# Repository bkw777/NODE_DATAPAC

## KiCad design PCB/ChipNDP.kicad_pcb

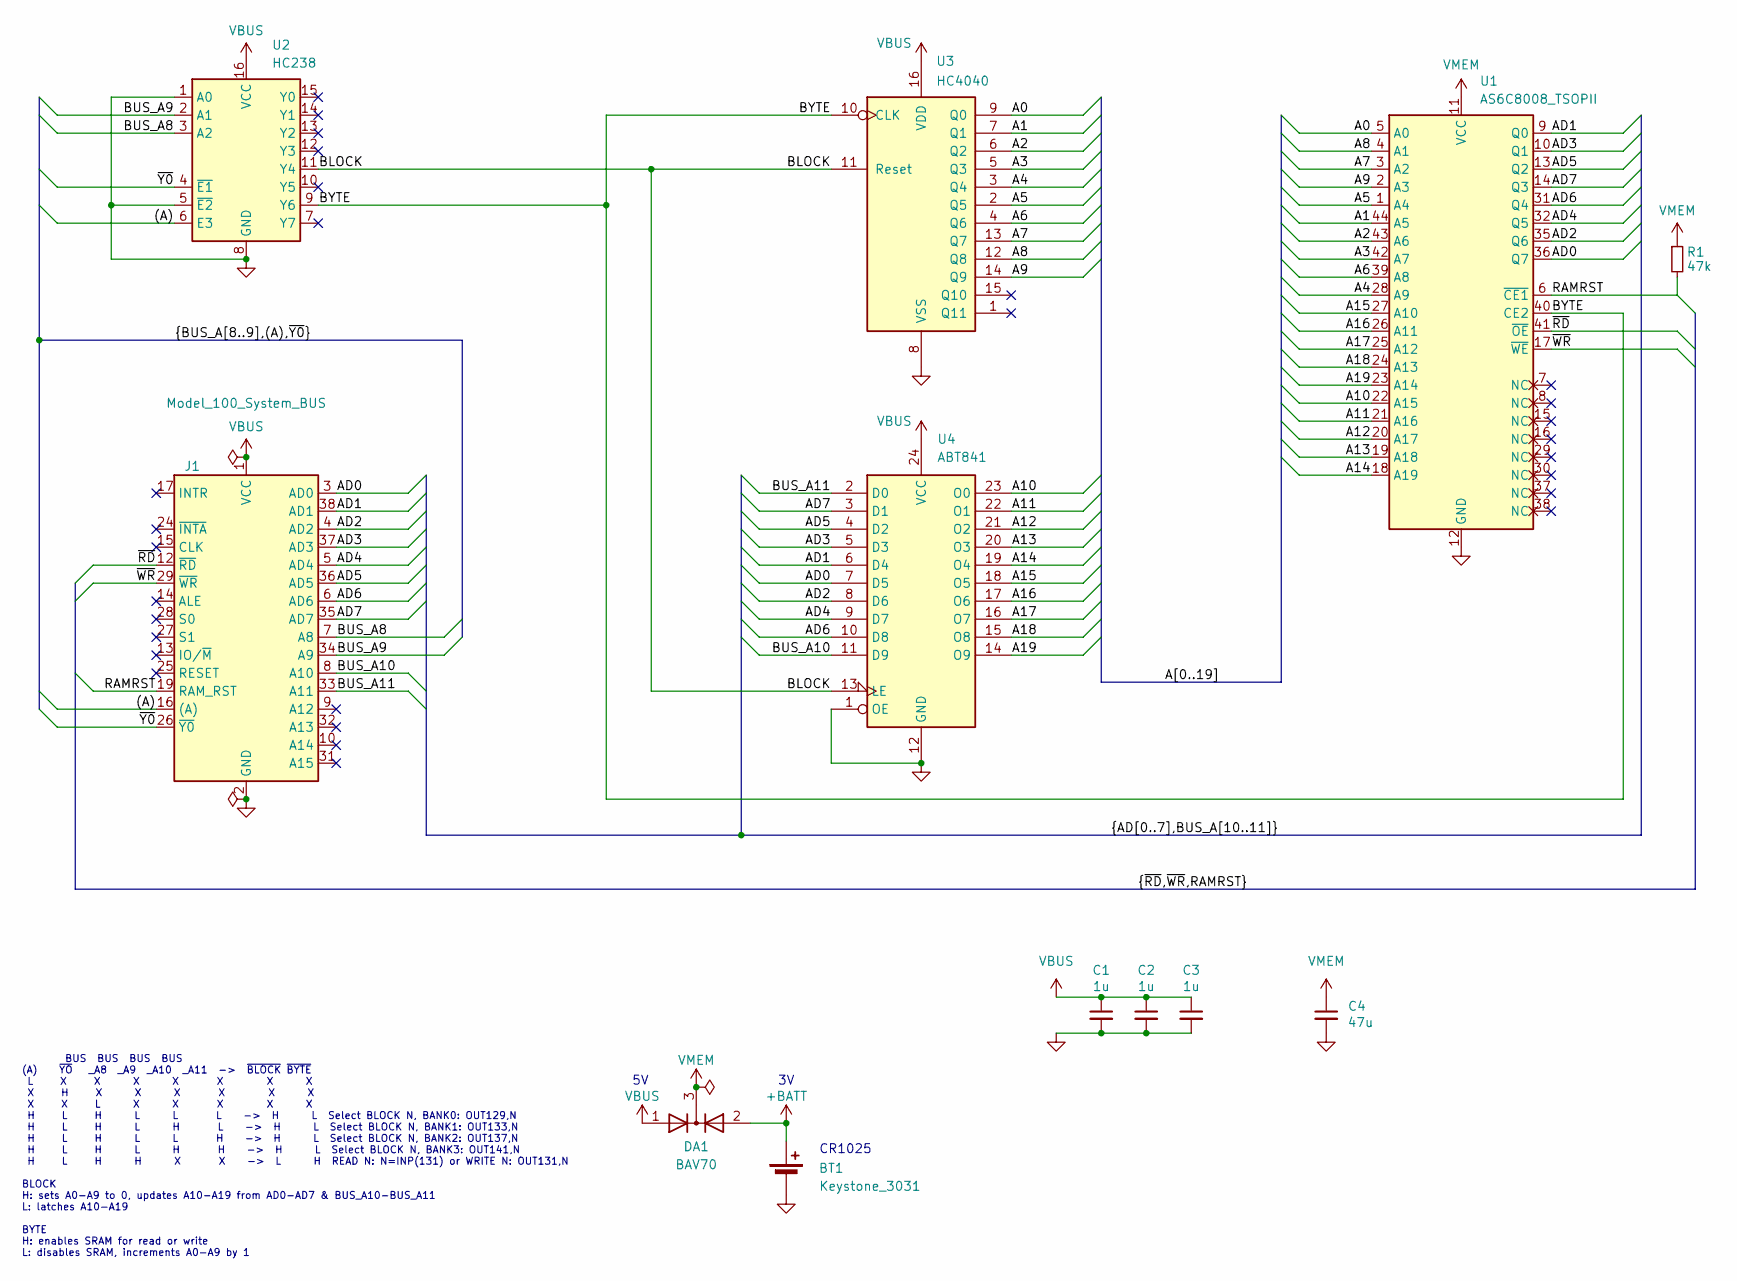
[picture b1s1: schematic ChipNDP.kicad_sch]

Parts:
BT1: Keystone_3031; MPN Keystone 3031
C1, C2, C3: 1u; C_0805; MPN CL21B105KAFNNNE
C4: 47u; C_1206; MPN C3216X5R1E476M160DC
DA1: BAV70; SOT-23; MPN BAV70-7-F
J1: Model_100_System_BUS; DIP-40_PCB; MPN 920-0172-01
R1: 47k; R_0805; MPN RMCF0805FT47K0
U1: AS6C8008_TSOPII; TSOP-II-44; MPN AS6C8008-55ZIN
U2: HC238; TSSOP-16; MPN 74HC238PW,118
U3: HC4040; TSSOP-16; MPN 74HC4040PW,118
U4: ABT841; TSSOP-24_4.4x7.8mm_P0.65mm; MPN SN74ABT841APW

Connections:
+BATT: BT1.1 (+), DA1.2 (A)
/(A): J1.16 ((A)), U2.6 (E3)
/A0: U1.5 (A0), U3.9 (Q0)
/A1: U1.44 (A5), U3.7 (Q1)
/A2: U1.43 (A6), U3.6 (Q2)
/A3: U1.42 (A7), U3.5 (Q3)
/A4: U1.28 (A9), U3.3 (Q4)
/A5: U1.1 (A4), U3.2 (Q5)
/A6: U1.39 (A8), U3.4 (Q6)
/A7: U1.3 (A2), U3.13 (Q7)
/A8: U1.4 (A1), U3.12 (Q8)
/A9: U1.2 (A3), U3.14 (Q9)
/A10: U1.22 (A15), U4.23 (O0)
/A11: U1.21 (A16), U4.22 (O1)
/A12: U1.20 (A17), U4.21 (O2)
/A13: U1.19 (A18), U4.20 (O3)
/A14: U1.18 (A19), U4.19 (O4)
/A15: U1.27 (A10), U4.18 (O5)
/A16: U1.26 (A11), U4.17 (O6)
/A17: U1.25 (A12), U4.16 (O7)
/A18: U1.24 (A13), U4.15 (O8)
/A19: U1.23 (A14), U4.14 (O9)
/AD0: J1.3 (AD0), U1.36 (Q7), U4.7 (D5)
/AD1: J1.38 (AD1), U1.9 (Q0), U4.6 (D4)
/AD2: J1.4 (AD2), U1.35 (Q6), U4.8 (D6)
/AD3: J1.37 (AD3), U1.10 (Q1), U4.5 (D3)
/AD4: J1.5 (AD4), U1.32 (Q5), U4.9 (D7)
/AD5: J1.36 (AD5), U1.13 (Q2), U4.4 (D2)
/AD6: J1.6 (AD6), U1.31 (Q4), U4.10 (D8)
/AD7: J1.35 (AD7), U1.14 (Q3), U4.3 (D1)
/BLOCK: U2.11 (Y4), U3.11 (Reset), U4.13 (LE)
/BUS_A8: J1.7 (A8), U2.3 (A2)
/BUS_A9: J1.34 (A9), U2.2 (A1)
/BUS_A10: J1.8 (A10), U4.11 (D9)
/BUS_A11: J1.33 (A11), U4.2 (D0)
/BYTE: U1.40 (CE2), U2.9 (Y6), U3.10 (CLK)
/RAMRST: J1.19 (RAM_RST), R1.2, U1.6 (~CE1)
/~RD: J1.12 (~RD), U1.41 (~OE)
/~WR: J1.29 (~WR), U1.17 (~WE)
/~Y0: J1.26 (~Y0), U2.4 (~E1)
GND: BT1.2 (-), C1.2, C2.2, C3.2, C4.2, J1.2 (GND), J1.11 (GND), J1.18 (GND), J1.23 (GND), J1.30 (GND), J1.39 (GND), U1.12 (GND), U1.34 (GND), U2.1 (A0), U2.5 (~E2), U2.8 (GND), U3.8 (VSS), U4.1 (OE), U4.12 (GND)
VBUS: C1.1, C2.1, C3.1, DA1.1 (A), J1.1 (VCC), J1.40 (VCC), U2.16 (VCC), U3.16 (VDD), U4.24 (VCC)
VMEM: C4.1, DA1.3 (K), R1.1, U1.11 (VCC), U1.33 (VCC)

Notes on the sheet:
BUS BUS BUS BUS (A) ~{YO} _A8 _A9 _A10 _A11 -> ~{BLOCK} ~{BYTE} L X X X X X X X X H X X X X X X X X L X X X X X H L H L L L -> H L Select BLOCK N, BANK0: OUT129,N H L H L H L -> H L Select BLOCK N, BANK1: OUT133,N H L H L L H -> H L Select BLOCK N, BANK2: OUT137,N H L H L H H -> H L Select BLOCK N,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
CR1025

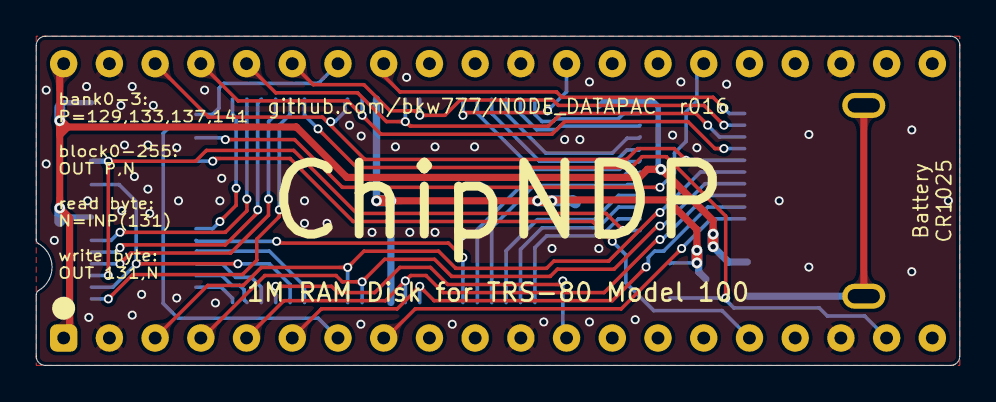
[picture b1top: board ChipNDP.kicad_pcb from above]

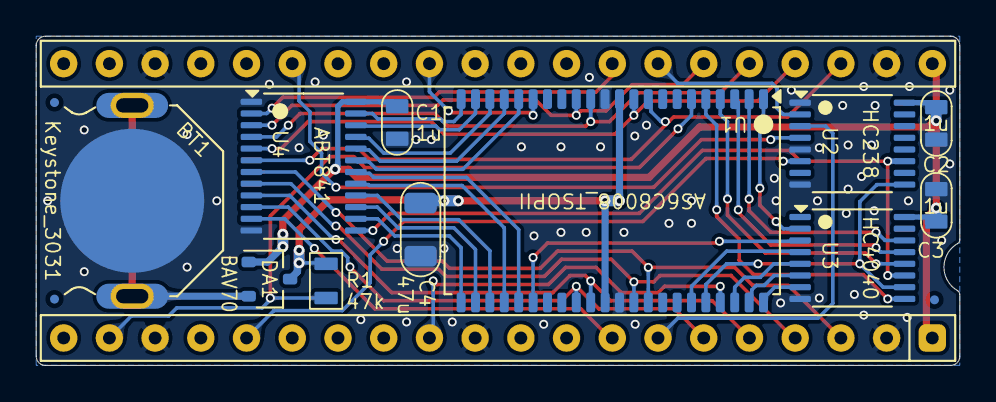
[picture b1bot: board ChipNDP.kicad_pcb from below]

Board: 2 copper layers, 51.3 x 18.3 mm, 15 parts (15 on the bottom side), 43 nets.

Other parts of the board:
F1, F2, F3: Fiducial_0.5_1.0

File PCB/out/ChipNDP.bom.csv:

"Reference","Value","Datasheet","Footprint","Qty","DNP","MPN","Description"
"BT1","Keystone_3031","datasheet/Keystone_3031.pdf","000_LOCAL:Keystone_3031","1","","Keystone 3031","Battery Retainer Coin, 10.0mm 1 Cell PC Pin"
"C1,C2,C3","1u","datasheets/CL21B105KAFNNNE.pdf","000_LOCAL:C_0805","3","","CL21B105KAFNNNE","CAP CER 1UF 25V X7R 0805"
"C4","47u","datasheets/TDK_MLCC_Cxxxx.pdf","000_LOCAL:C_1206","1","","C3216X5R1E476M160DC","CAP CER 47UF 25V X5R 1206"
"DA1","BAV70","datasheets/BAV70.pdf","000_LOCAL:SOT-23","1","","BAV70-7-F","DIODE ARRAY GP 75V 150MA SOT23-3"
"J1","Model_100_System_BUS","datasheets/TRS-80_Model_100_User_Guide.pdf","000_LOCAL:DIP-40_PCB","1","","920-0172-01","CONN HEADER VERT 40P 2.54MM"
"R1","47k","datasheets/sei-rmcf_rmcp.pdf","000_LOCAL:R_0805","1","","RMCF0805FT47K0","RES 47K OHM 1% 1/8W 0805"
"U1","AS6C8008_TSOPII","datasheets/AS6C8008.pdf","000_LOCAL:TSOP-II-44","1","","AS6C8008-55ZIN","IC SRAM 1Mx8 PARALLEL 5v TSOP-II-44"
"U2","HC238","datasheets/HC238.pdf","000_LOCAL:TSSOP-16","1","","74HC238PW,118","IC DECODER/DEMUX 1 X 3:8 16SO"
"U3","HC4040","datasheets/4040.pdf","000_LOCAL:TSSOP-16","1","","74HC4040PW,118","IC BINARY COUNTER 12-BIT 16SO"
"U4","ABT841","datasheets/sn54abt841.pdf","000_LOCAL:TSSOP-24_4.4x7.8mm_P0.65mm","1","","SN74ABT841APW","IC 10BIT LATCH 3-STATE 24-SOIC"

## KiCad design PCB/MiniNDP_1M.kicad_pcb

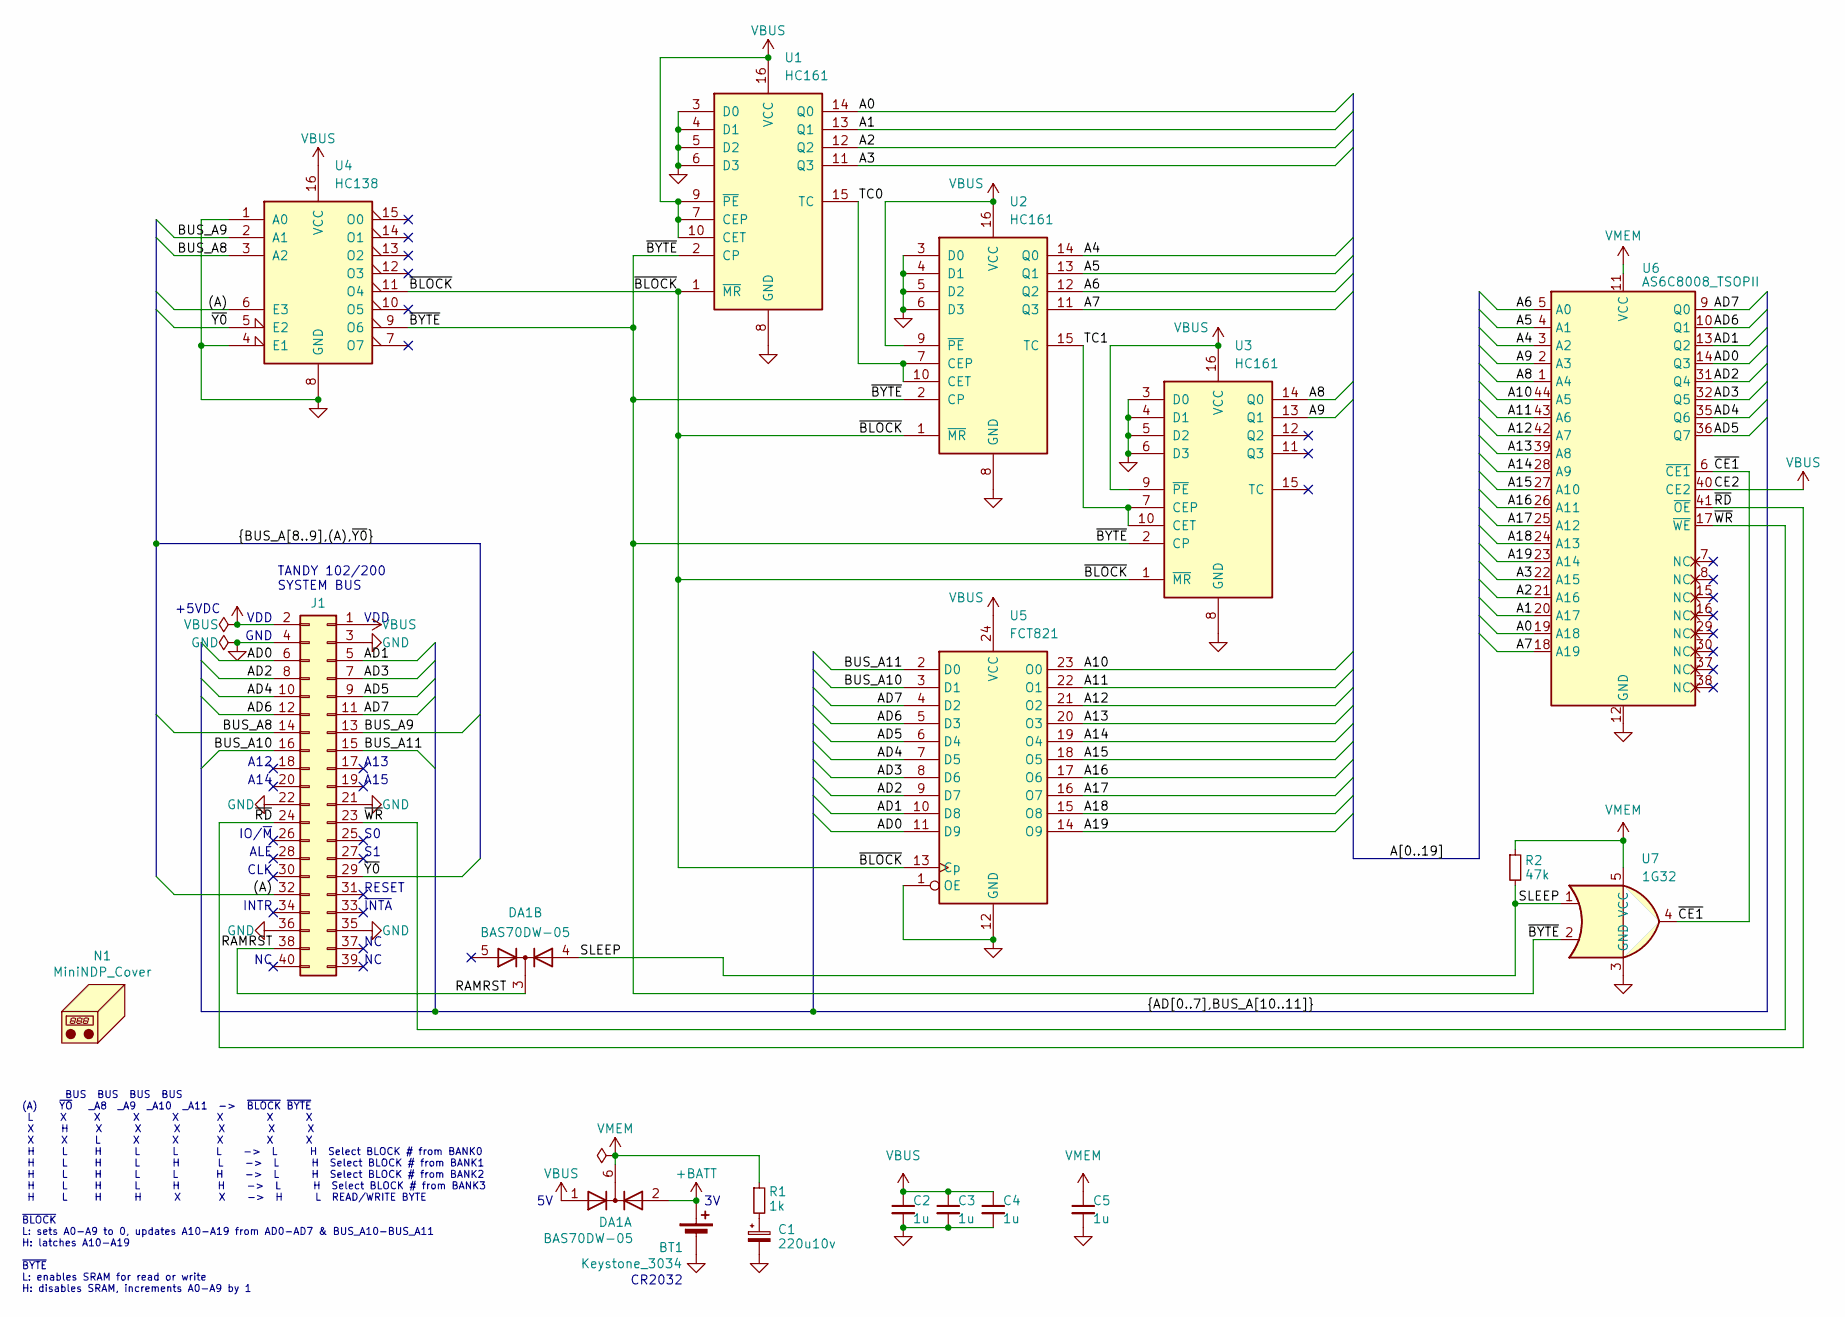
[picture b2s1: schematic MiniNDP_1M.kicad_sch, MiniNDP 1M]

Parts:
BT1: Keystone_3034; Keystone_3028_3034; MPN Keystone 3034
C1: 220u10v; CP_6032; MPN TAJC227K010RNJ
C2, C3, C4, C5: 1u; C_0805; MPN CL21B105KAFNNNE
DA1: BAS70DW-05; SOT-363_SC-70-6_symmetric; MPN BAS70DW-05-7-F
J1: Conn_02x20_Odd_Even; IDC-Header_2x20_P2.54mm_Vertical; MPN 302-S401
N1: MiniNDP_Cover; MPN MiniNDP_Cover.stl
R1: 1k; R_0805; MPN RK73B2ATTD102J
R2: 47k; R_0805; MPN RMCF0805FT47K0
U1, U2, U3: HC161; TSSOP-16; MPN 74HC161PW,118
U4: HC138; TSSOP-16; MPN 74HC138PW,118
U5: FCT821; SOIC-24; MPN CY74FCT821BTSOC
U6: AS6C8008_TSOPII; TSOP-II-44; MPN AS6C8008-55ZIN
U7: 1G32; SOT-353_SC-70-5; MPN 74LVC1G32GW,125

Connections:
+BATT: BT1.1 (+), DA1.2 (A)
/(A): J1.32, U4.6 (E3)
/A0: U1.14 (Q0), U6.19 (A18)
/A1: U1.13 (Q1), U6.20 (A17)
/A2: U1.12 (Q2), U6.21 (A16)
/A3: U1.11 (Q3), U6.22 (A15)
/A4: U2.14 (Q0), U6.3 (A2)
/A5: U2.13 (Q1), U6.4 (A1)
/A6: U2.12 (Q2), U6.5 (A0)
/A7: U2.11 (Q3), U6.18 (A19)
/A8: U3.14 (Q0), U6.1 (A4)
/A9: U3.13 (Q1), U6.2 (A3)
/A10: U5.23 (O0), U6.44 (A5)
/A11: U5.22 (O1), U6.43 (A6)
/A12: U5.21 (O2), U6.42 (A7)
/A13: U5.20 (O3), U6.39 (A8)
/A14: U5.19 (O4), U6.28 (A9)
/A15: U5.18 (O5), U6.27 (A10)
/A16: U5.17 (O6), U6.26 (A11)
/A17: U5.16 (O7), U6.25 (A12)
/A18: U5.15 (O8), U6.24 (A13)
/A19: U5.14 (O9), U6.23 (A14)
/AD0: J1.6, U5.11 (D9), U6.14 (Q3)
/AD1: J1.5, U5.10 (D8), U6.13 (Q2)
/AD2: J1.8, U5.9 (D7), U6.31 (Q4)
/AD3: J1.7, U5.8 (D6), U6.32 (Q5)
/AD4: J1.10, U5.7 (D5), U6.35 (Q6)
/AD5: J1.9, U5.6 (D4), U6.36 (Q7)
/AD6: J1.12, U5.5 (D3), U6.10 (Q1)
/AD7: J1.11, U5.4 (D2), U6.9 (Q0)
/BUS_A8: J1.14, U4.3 (A2)
/BUS_A9: J1.13, U4.2 (A1)
/BUS_A10: J1.16, U5.3 (D1)
/BUS_A11: J1.15, U5.2 (D0)
/RAMRST: DA1.3 (K), J1.38
/SLEEP: DA1.4 (A), R2.2, U7.1
/TC0: U1.15 (TC), U2.7 (CEP), U2.10 (CET)
/TC1: U2.15 (TC), U3.7 (CEP), U3.10 (CET)
/~BLOCK: U1.1 (~MR), U2.1 (~MR), U3.1 (~MR), U4.11 (O4), U5.13 (Cp)
/~BYTE: U1.2 (CP), U2.2 (CP), U3.2 (CP), U4.9 (O6), U7.2
/~CE1: U6.6 (~CE1), U7.4
/~RD: J1.24, U6.41 (~OE)
/~WR: J1.23, U6.17 (~WE)
/~Y0: J1.29, U4.5 (E2)
GND: BT1.2 (-), C1.2, C2.2, C3.2, C4.2, C5.2, J1.3, J1.4, J1.21, J1.22, J1.35, J1.36, U1.3 (D0), U1.4 (D1), U1.5 (D2), U1.6 (D3), U1.8 (GND), U2.3 (D0), U2.4 (D1), U2.5 (D2), U2.6 (D3), U2.8 (GND), U3.3 (D0), U3.4 (D1), U3.5 (D2), U3.6 (D3), U3.8 (GND), U4.1 (A0), U4.4 (E1), U4.8 (GND), U5.1 (OE), U5.12 (GND), U6.12 (GND), U6.34 (GND), U7.3 (GND)
unnamed: C1.1, R1.2
VBUS: C2.1, C3.1, C4.1, DA1.1 (A), J1.1, J1.2, U1.7 (CEP), U1.9 (~PE), U1.10 (CET), U1.16 (VCC), U2.9 (~PE), U2.16 (VCC), U3.9 (~PE), U3.16 (VCC), U4.16 (VCC), U5.24 (VCC), U6.40 (CE2)
VMEM: C5.1, DA1.6 (K), R1.1, R2.1, U6.11 (VCC), U6.33 (VCC), U7.5 (VCC)

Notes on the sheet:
TANDY 102/200 SYSTEM BUS
+5VDC
A15
CR2032
INTR
A14
ALE
~{INTA}
CLK
GND
IO/~{M}
VDD
BUS BUS BUS BUS (A) ~{YO} _A8 _A9 _A10 _A11 -> ~{BLOCK} ~{BYTE} L X X X X X X X X H X X X X X X X X L X X X X X H L H L L L -> L H Select BLOCK # from BANK0 H L H L H L -> L H Select BLOCK # from BANK1 H L H L L H -> L H Select BLOCK # from BANK2 H L H L H H -> L H Select BLOCK # from BANK3 H L H H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
RESET
A13
A12

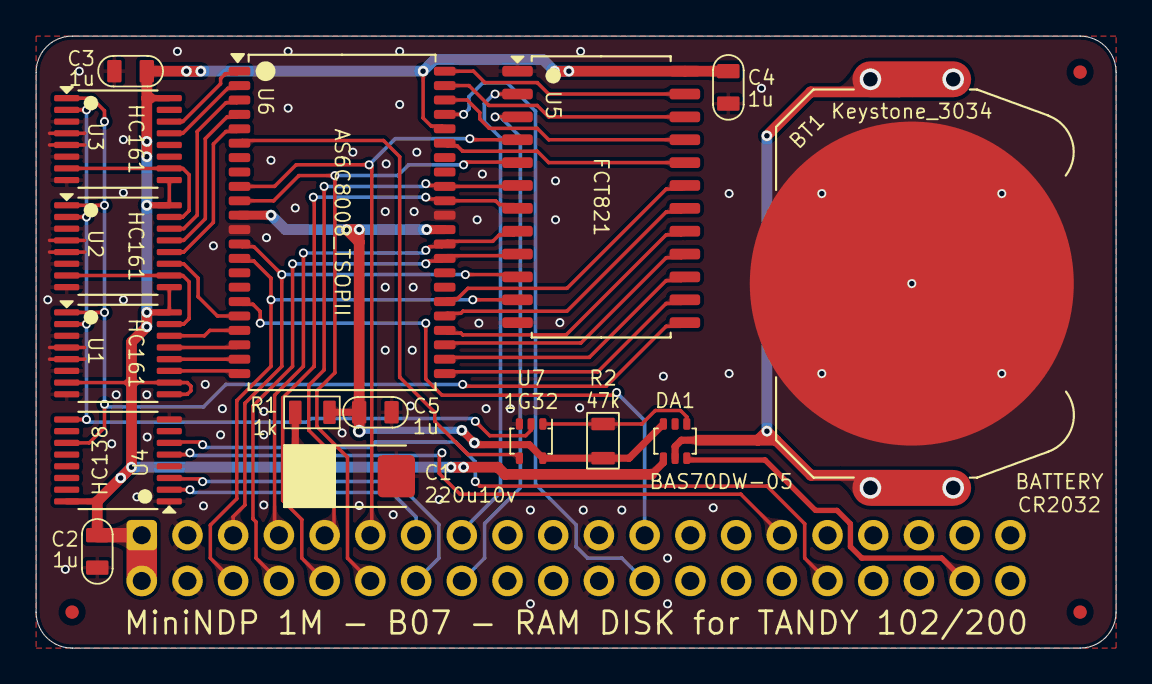
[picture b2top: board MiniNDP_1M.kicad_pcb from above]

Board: 2 copper layers, 60.0 x 34.0 mm, 21 parts (1 on the bottom side), 48 nets.

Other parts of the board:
F2, F2#2, F3: Fiducial_0.75_1.5

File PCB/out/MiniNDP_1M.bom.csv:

"Reference","Value","Datasheet","Footprint","Qty","DNP","MPN","Description"
"BT1","Keystone_3034","datasheets/Keystone_3034.pdf","000_LOCAL:Keystone_3028_3034","1","","Keystone 3034","SMT 20mm x 3.2mm coin cell holder"
"C1","220u10v","datasheets/TAJ.odf","000_LOCAL:CP_6032","1","","TAJC227K010RNJ","CAP TANT 220UF 10% 10V 2312"
"C2,C3,C4,C5","1u","datasheets/CL21B105KAFNNNE.pdf","000_LOCAL:C_0805","4","","CL21B105KAFNNNE","CAP CER 1UF 25V X7R 0805"
"DA1","BAS70DW-05","datasheets/BAS70.pdf","000_LOCAL:SOT-363_SC-70-6_symmetric","1","","BAS70DW-05-7-F","DIODE ARR SCHOTT 70V 70MA SOT363 2-PAIR COMMON-CATHODE"
"J1","Conn_02x20_Odd_Even","datasheets/2x20_male_boxed.pdf","000_LOCAL:IDC-Header_2x20_P2.54mm_Vertical","1","","302-S401","CONN HEADER VERT 40POS 2.54MM"
"R1","1k","datasheets/RK73.pdf","000_LOCAL:R_0805","1","","RK73B2ATTD102J","RES 1K OHM 5% 1/4W 0805"
"R2","47k","datasheets/sei-rmcf_rmcp.pdf","000_LOCAL:R_0805","1","","RMCF0805FT47K0","RES 47K OHM 1% 1/8W 0805"
"U1,U2,U3","HC161","datasheets/HC161.pdf","000_LOCAL:TSSOP-16","3","","74HC161PW,118","IC BINARY COUNTER 4-BIT 16TSSOP"
"U4","HC138","datasheets/HC138.pdf","000_LOCAL:TSSOP-16","1","","74HC138PW,118","IC DECODER/DEMUX 1X3:8 16TSSOP"
"U5","FCT821","datasheets/CY74FCT821T.pdf","000_LOCAL:SOIC-24","1","","CY74FCT821BTSOC","IC FF D-TYPE SNGL 10BIT 24SOIC"
"U6","AS6C8008_TSOPII","datasheets/AS6C8008.pdf","000_LOCAL:TSOP-II-44","1","","AS6C8008-55ZIN","IC SRAM 1Mx8 PARALLEL 5v TSOP-II-44"
"U7","1G32","datasheets/LVC1G32.pdf","000_LOCAL:SOT-353_SC-70-5","1","","74LVC1G32GW,125","IC GATE OR 1CH 2-INP 5TSSOP"

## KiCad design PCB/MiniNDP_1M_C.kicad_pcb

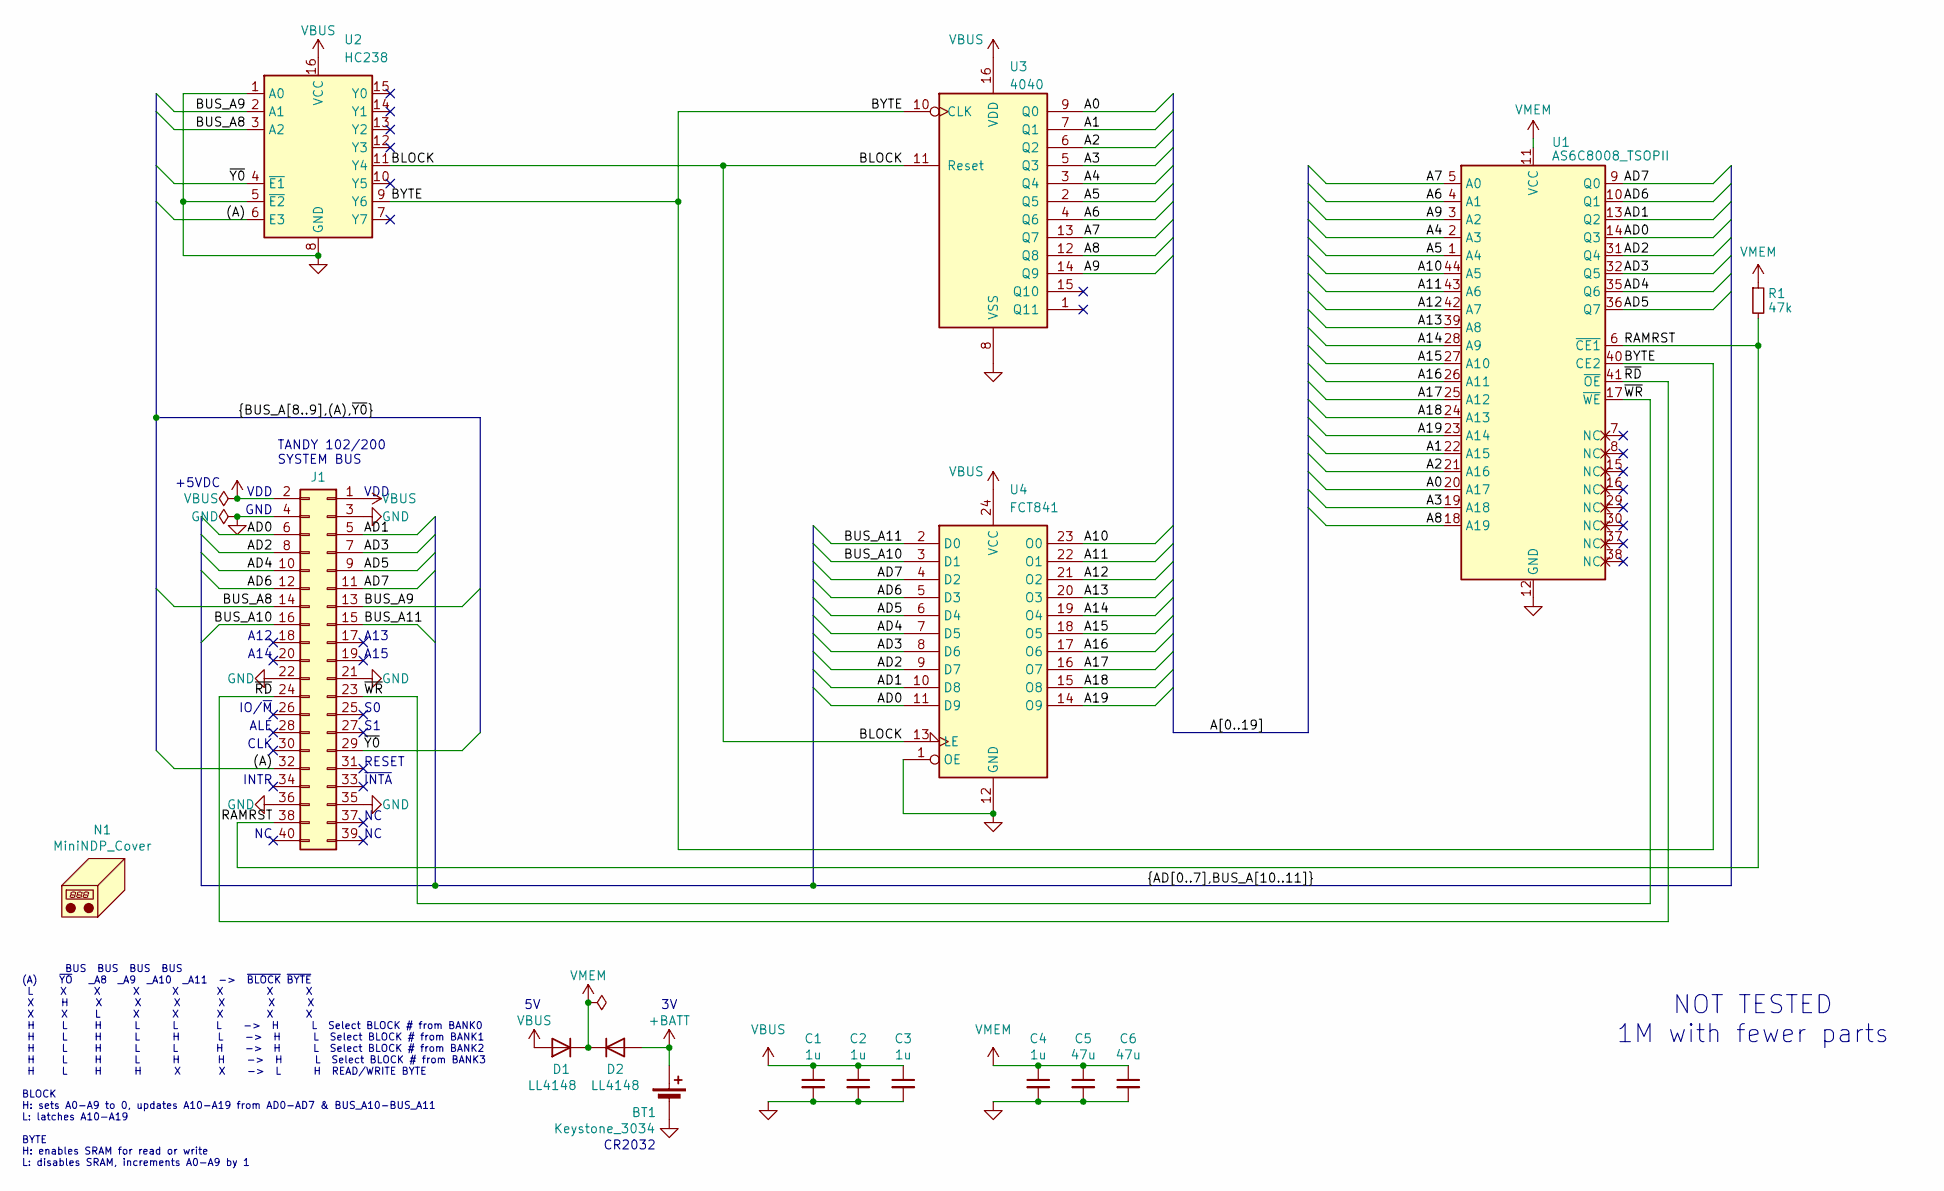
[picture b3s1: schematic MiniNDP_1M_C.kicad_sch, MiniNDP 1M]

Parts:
BT1: Keystone_3034; Keystone_3028_3034; MPN Keystone 3034
C1, C2, C3, C4: 1u; C_0805; MPN CL21B105KAFNNNE
C5, C6: 47u; C_1206; MPN C3216X5R1E476M160DC
D1, D2: LL4148; D_MiniMELF; MPN FDLL4148
J1: Conn_02x20_Odd_Even; IDC-Header_2x20_P2.54mm_Vertical; MPN 302-S401
N1: MiniNDP_Cover; MPN MiniNDP_Cover.stl
R1: 47k; R_0805; MPN RMCF0805FT47K0
U1: AS6C8008_TSOPII; TSOP-II-44; MPN AS6C8008-55ZIN
U2: HC238; SOIC-16_3.9x9.9mm_P1.27mm; MPN 74HC238D,653
U3: 4040; SOIC-16_3.9x9.9mm_P1.27mm; MPN 74HC4040D,653
U4: FCT841; SOIC-24; MPN CY74FCT841CTSOC

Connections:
+BATT: BT1.1 (+), D2.2 (A)
/(A): J1.32, U2.6 (E3)
/A0: U1.20 (A17), U3.9 (Q0)
/A1: U1.22 (A15), U3.7 (Q1)
/A2: U1.21 (A16), U3.6 (Q2)
/A3: U1.19 (A18), U3.5 (Q3)
/A4: U1.2 (A3), U3.3 (Q4)
/A5: U1.1 (A4), U3.2 (Q5)
/A6: U1.4 (A1), U3.4 (Q6)
/A7: U1.5 (A0), U3.13 (Q7)
/A8: U1.18 (A19), U3.12 (Q8)
/A9: U1.3 (A2), U3.14 (Q9)
/A10: U1.44 (A5), U4.23 (O0)
/A11: U1.43 (A6), U4.22 (O1)
/A12: U1.42 (A7), U4.21 (O2)
/A13: U1.39 (A8), U4.20 (O3)
/A14: U1.28 (A9), U4.19 (O4)
/A15: U1.27 (A10), U4.18 (O5)
/A16: U1.26 (A11), U4.17 (O6)
/A17: U1.25 (A12), U4.16 (O7)
/A18: U1.24 (A13), U4.15 (O8)
/A19: U1.23 (A14), U4.14 (O9)
/AD0: J1.6, U1.14 (Q3), U4.11 (D9)
/AD1: J1.5, U1.13 (Q2), U4.10 (D8)
/AD2: J1.8, U1.31 (Q4), U4.9 (D7)
/AD3: J1.7, U1.32 (Q5), U4.8 (D6)
/AD4: J1.10, U1.35 (Q6), U4.7 (D5)
/AD5: J1.9, U1.36 (Q7), U4.6 (D4)
/AD6: J1.12, U1.10 (Q1), U4.5 (D3)
/AD7: J1.11, U1.9 (Q0), U4.4 (D2)
/BLOCK: U2.11 (Y4), U3.11 (Reset), U4.13 (LE)
/BUS_A8: J1.14, U2.3 (A2)
/BUS_A9: J1.13, U2.2 (A1)
/BUS_A10: J1.16, U4.3 (D1)
/BUS_A11: J1.15, U4.2 (D0)
/BYTE: U1.40 (CE2), U2.9 (Y6), U3.10 (CLK)
/RAMRST: J1.38, R1.2, U1.6 (~CE1)
/~RD: J1.24, U1.41 (~OE)
/~WR: J1.23, U1.17 (~WE)
/~Y0: J1.29, U2.4 (~E1)
GND: BT1.2 (-), C1.2, C2.2, C3.2, C4.2, C5.2, C6.2, J1.3, J1.4, J1.21, J1.22, J1.35, J1.36, U1.12 (GND), U1.34 (GND), U2.1 (A0), U2.5 (~E2), U2.8 (GND), U3.8 (VSS), U4.1 (OE), U4.12 (GND)
VBUS: C1.1, C2.1, C3.1, D1.2 (A), J1.1, J1.2, U2.16 (VCC), U3.16 (VDD), U4.24 (VCC)
VMEM: C4.1, C5.1, C6.1, D1.1 (K), D2.1 (K), R1.1, U1.11 (VCC), U1.33 (VCC)

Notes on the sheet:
TANDY 102/200 SYSTEM BUS
+5VDC
A15
CR2032
INTR
A14
ALE
~{INTA}
CLK
GND
IO/~{M}
VDD
BUS BUS BUS BUS (A) ~{YO} _A8 _A9 _A10 _A11 -> ~{BLOCK} ~{BYTE} L X X X X X X X X H X X X X X X X X L X X X X X H L H L L L -> H L Select BLOCK # from BANK0 H L H L H L -> H L Select BLOCK # from BANK1 H L H L L H -> H L Select BLOCK # from BANK2 H L H L H H -> H L Select BLOCK # from BANK3 H L H H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
RESET
A13
A12
NOT TESTED 1M with fewer parts

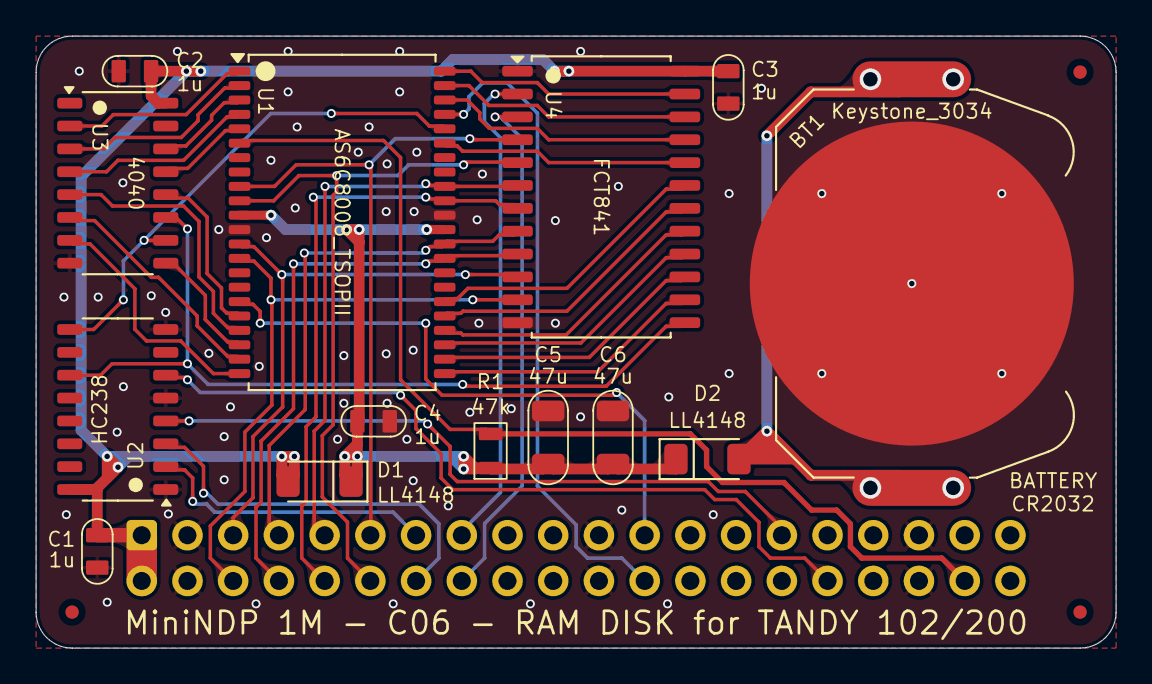
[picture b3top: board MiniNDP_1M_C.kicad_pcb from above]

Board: 2 copper layers, 60.0 x 34.0 mm, 19 parts (1 on the bottom side), 43 nets.

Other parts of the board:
F2, F2#2, F3: Fiducial_0.75_1.5

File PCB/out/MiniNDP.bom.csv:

"Reference","Value","Datasheet","Footprint","Qty","DNP","MPN","Description"
"BT1","Keystone_3034","datasheets/Keystone_3034.pdf","000_LOCAL:Keystone_3028_3034","1","","Keystone 3034","SMT 20mm x 3.2mm coin cell holder"
"C1,C2,C3,C4,C5","1u","datasheets/CL21B105KAFNNNE.pdf","000_LOCAL:C_0805","5","","CL21B105KAFNNNE","CAP CER 1UF 25V X7R 0805"
"C6,C7","47u","datasheets/TDK_MLCC_Cxxxx.pdf","000_LOCAL:C_1206","2","","C3216X5R1E476M160DC","CAP CER 47UF 25V X5R 1206"
"D1,D2","LL4148","datasheets/ll4148.pdf","000_LOCAL:D_MiniMELF","2","","FDLL4148","50V 1A General Purpose Rectifier Diode"
"J1","Conn_02x20_Odd_Even","datasheets/2x20_male_boxed.pdf","000_LOCAL:IDC-Header_2x20_P2.54mm_Vertical","1","","302-S401","CONN HEADER VERT 40POS 2.54MM"
"R1","47k","datasheets/sei-rmcf_rmcp.pdf","000_LOCAL:R_0805","1","","RMCF0805FT47K0","RES 47K OHM 1% 1/8W 0805"
"U1","AS6C8008_TSOPII","datasheets/AS6C8008.pdf","000_LOCAL:TSOP-II-44","1","","AS6C8008-55ZIN","IC SRAM 1Mx8 PARALLEL 5v TSOP-II-44"
"U2","HC238","datasheets/HC238.pdf","000_LOCAL:SOIC-16_3.9x9.9mm_P1.27mm","1","","74HC238D,653","IC DECODER/DEMUX 1 X 3:8 16SO"
"U3","HC4040","datasheets/4040.pdf","000_LOCAL:SOIC-16_3.9x9.9mm_P1.27mm","1","","74HC4040D,653","IC BINARY COUNTER 12-BIT 16SO"
"U4","FCT841","datasheets/FCT841.pdf","000_LOCAL:SOIC-24","1","","CY74FCT841CTSOC","IC 10BIT LATCH 3-STATE 24-SOIC"

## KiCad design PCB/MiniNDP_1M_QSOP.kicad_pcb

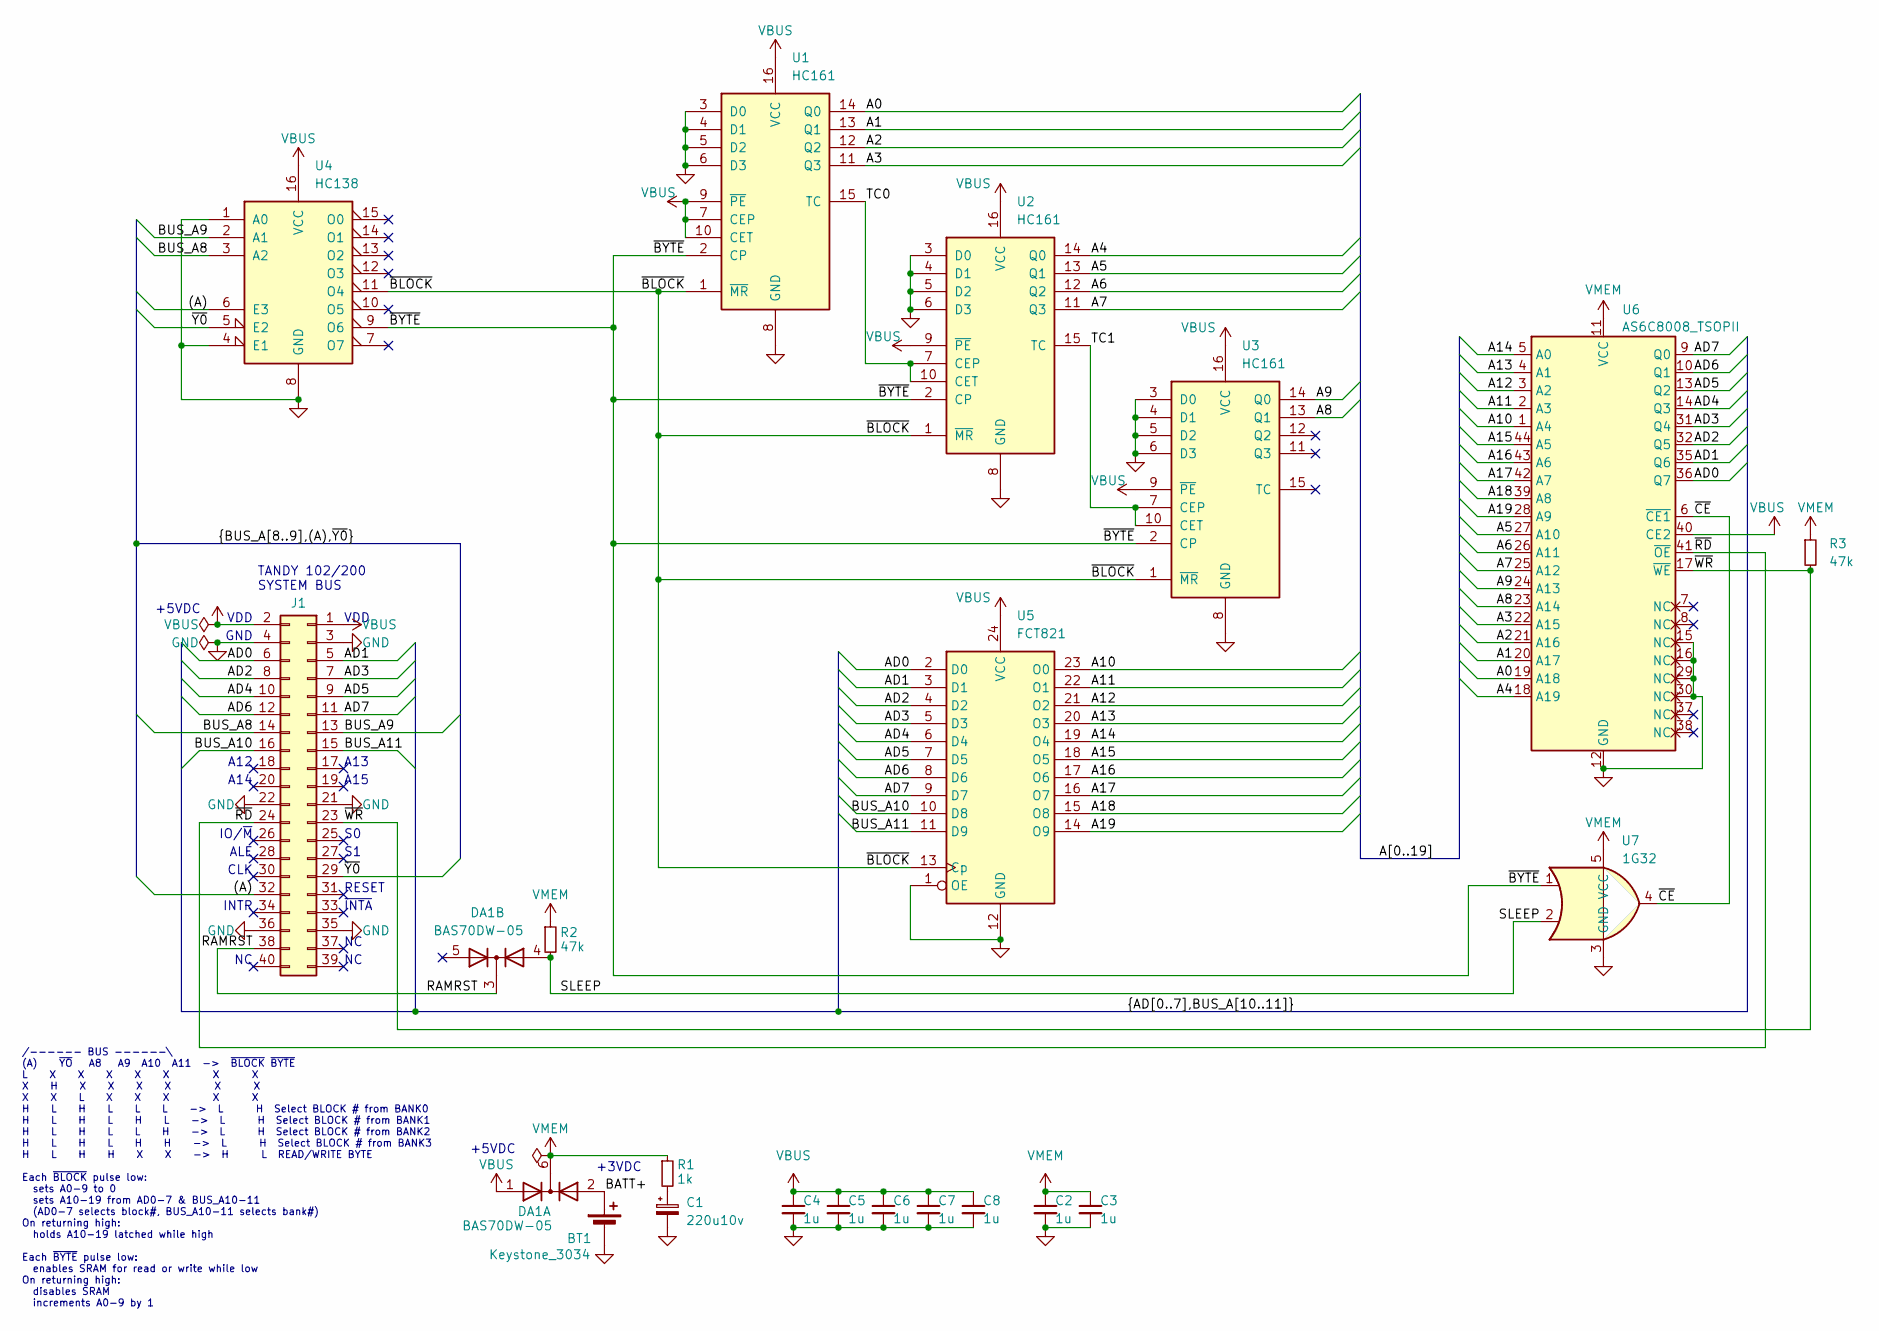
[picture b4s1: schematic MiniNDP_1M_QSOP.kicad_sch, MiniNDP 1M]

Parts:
BT1: Keystone_3034; Keystone_3028_3034
C1: 220u10v; CP_6032
C2, C3, C4, C5, C6, C7, C8: 1u; C_0805
DA1: BAS70DW-05; SOT-363_SC-70-6_symmetric
J1: Conn_02x20_Odd_Even; IDC-Header_2x20_P2.54mm_Vertical
R1: 1k; R_0805
R2, R3: 47k; R_0805
U1, U2, U3: HC161; TSSOP-16
U4: HC138; TSSOP-16
U5: FCT821; SSOP-24
U6: AS6C8008_TSOPII; TSOP-II-44
U7: 1G32; SOT-353_SC-70-5

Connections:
/(A): J1.32, U4.6 (E3)
/A0: U1.14 (Q0), U6.19 (A18)
/A1: U1.13 (Q1), U6.20 (A17)
/A2: U1.12 (Q2), U6.21 (A16)
/A3: U1.11 (Q3), U6.22 (A15)
/A4: U2.14 (Q0), U6.18 (A19)
/A5: U2.13 (Q1), U6.27 (A10)
/A6: U2.12 (Q2), U6.26 (A11)
/A7: U2.11 (Q3), U6.25 (A12)
/A8: U3.13 (Q1), U6.23 (A14)
/A9: U3.14 (Q0), U6.24 (A13)
/A10: U5.23 (O0), U6.1 (A4)
/A11: U5.22 (O1), U6.2 (A3)
/A12: U5.21 (O2), U6.3 (A2)
/A13: U5.20 (O3), U6.4 (A1)
/A14: U5.19 (O4), U6.5 (A0)
/A15: U5.18 (O5), U6.44 (A5)
/A16: U5.17 (O6), U6.43 (A6)
/A17: U5.16 (O7), U6.42 (A7)
/A18: U5.15 (O8), U6.39 (A8)
/A19: U5.14 (O9), U6.28 (A9)
/AD0: J1.6, U5.2 (D0), U6.36 (Q7)
/AD1: J1.5, U5.3 (D1), U6.35 (Q6)
/AD2: J1.8, U5.4 (D2), U6.32 (Q5)
/AD3: J1.7, U5.5 (D3), U6.31 (Q4)
/AD4: J1.10, U5.6 (D4), U6.14 (Q3)
/AD5: J1.9, U5.7 (D5), U6.13 (Q2)
/AD6: J1.12, U5.8 (D6), U6.10 (Q1)
/AD7: J1.11, U5.9 (D7), U6.9 (Q0)
/BATT+: BT1.1 (+), DA1.2 (A)
/BUS_A8: J1.14, U4.3 (A2)
/BUS_A9: J1.13, U4.2 (A1)
/BUS_A10: J1.16, U5.10 (D8)
/BUS_A11: J1.15, U5.11 (D9)
/RAMRST: DA1.3 (K), J1.38
/SLEEP: DA1.4 (A), R2.2, U7.2
/TC0: U1.15 (TC), U2.7 (CEP), U2.10 (CET)
/TC1: U2.15 (TC), U3.7 (CEP), U3.10 (CET)
/~BLOCK: U1.1 (~MR), U2.1 (~MR), U3.1 (~MR), U4.11 (O4), U5.13 (Cp)
/~BYTE: U1.2 (CP), U2.2 (CP), U3.2 (CP), U4.9 (O6), U7.1
/~CE: U6.6 (~CE1), U7.4
/~RD: J1.24, U6.41 (~OE)
/~WR: J1.23, R3.2, U6.17 (~WE)
/~Y0: J1.29, U4.5 (E2)
GND: BT1.2 (-), C1.2, C2.2, C3.2, C4.2, C5.2, C6.2, C7.2, C8.2, J1.3, J1.4, J1.21, J1.22, J1.35, J1.36, U1.3 (D0), U1.4 (D1), U1.5 (D2), U1.6 (D3), U1.8 (GND), U2.3 (D0), U2.4 (D1), U2.5 (D2), U2.6 (D3), U2.8 (GND), U3.3 (D0), U3.4 (D1), U3.5 (D2), U3.6 (D3), U3.8 (GND), U4.1 (A0), U4.4 (E1), U4.8 (GND), U5.1 (OE), U5.12 (GND), U6.12 (GND), U6.15 (NC), U6.16 (NC), U6.29 (NC), U6.30 (NC), U6.34 (GND), U7.3 (GND)
unnamed: C1.1, R1.2
VBUS: C4.1, C5.1, C6.1, C7.1, C8.1, DA1.1 (A), J1.1, J1.2, U1.7 (CEP), U1.9 (~PE), U1.10 (CET), U1.16 (VCC), U2.9 (~PE), U2.16 (VCC), U3.9 (~PE), U3.16 (VCC), U4.16 (VCC), U5.24 (VCC), U6.40 (CE2)
VMEM: C2.1, C3.1, DA1.6 (K), R1.1, R2.1, R3.1, U6.11 (VCC), U6.33 (VCC), U7.5 (VCC)

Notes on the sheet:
TANDY 102/200 SYSTEM BUS
+5VDC
A15
INTR
A14
ALE
~{INTA}
CLK
GND
IO/~{M}
VDD
/------ BUS ------\ (A) ~{YO} A8 A9 A10 A11 -> ~{BLOCK} ~{BYTE} L X X X X X X X X H X X X X X X X X L X X X X X H L H L L L -> L H Select BLOCK # from BANK0 H L H L H L -> L H Select BLOCK # from BANK1 H L H L L H -> L H Select BLOCK # from BANK2 H L H L H H -> L H Select BLOCK # from BANK3 H L H H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
+3VDC
RESET
A13
A12

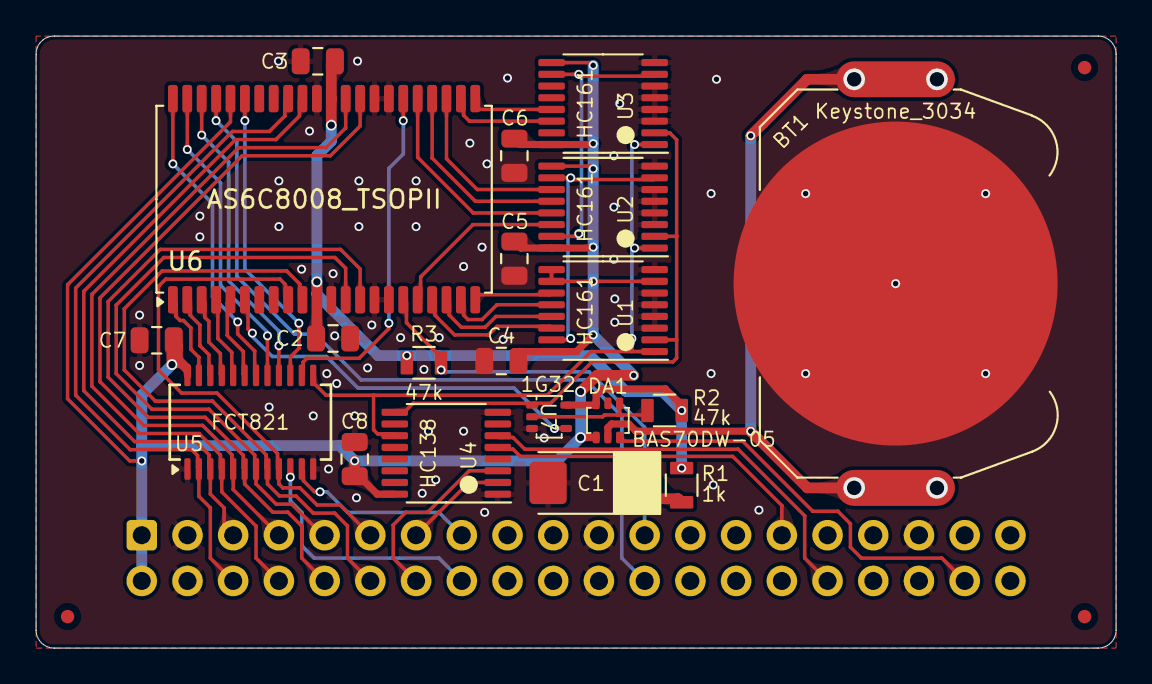
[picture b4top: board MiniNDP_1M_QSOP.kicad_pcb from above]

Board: 2 copper layers, 60.0 x 34.0 mm, 24 parts (1 on the bottom side), 48 nets.

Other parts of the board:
F1, F2, F3: Fiducial_0.75_1.5

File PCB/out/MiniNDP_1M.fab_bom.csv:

"Reference","Value","Datasheet","Footprint","Qty","DNP","MPN","Description"
"BT1","Keystone_3034","datasheets/Keystone_3034.pdf","000_LOCAL:Keystone_3028_3034","1","","Keystone 3034","SMT 20mm x 3.2mm coin cell holder"
"C1","220u10v","datasheets/TAJ.odf","000_LOCAL:CP_6032","1","","TAJC227K010RNJ","CAP TANT 220UF 10% 10V 2312"
"C2,C3,C4,C5","1u","datasheets/CL21B105KAFNNNE.pdf","000_LOCAL:C_0805","4","","CL21B105KAFNNNE","CAP CER 1UF 25V X7R 0805"
"DA1","BAS70DW-05","datasheets/BAS70.pdf","000_LOCAL:SOT-363_SC-70-6_symmetric","1","","BAS70DW-05-7-F","DIODE ARR SCHOTT 70V 70MA SOT363 2-PAIR COMMON-CATHODE"
"J1","Conn_02x20_Odd_Even","datasheets/2x20_male_boxed.pdf","000_LOCAL:IDC-Header_2x20_P2.54mm_Vertical","1","","302-S401","CONN HEADER VERT 40POS 2.54MM"
"R1","1k","datasheets/RK73.pdf","000_LOCAL:R_0805","1","","RK73B2ATTD102J","RES 1K OHM 5% 1/4W 0805"
"R2,R3","47k","-- mixed values --","000_LOCAL:R_0805","2","","RMCF0805FT47K0","RES 47K OHM 1% 1/8W 0805"
"U1,U2,U3","HC161","datasheets/HC161.pdf","000_LOCAL:TSSOP-16","3","","74HC161PW,118","IC BINARY COUNTER 4-BIT 16TSSOP"
"U4","HC138","datasheets/HC138.pdf","000_LOCAL:TSSOP-16","1","","74HC138PW,118","IC DECODER/DEMUX 1X3:8 16TSSOP"
"U5","FCT821","datasheets/CY74FCT821T.pdf","000_LOCAL:SOIC-24","1","","CY74FCT821BTSOC","IC FF D-TYPE SNGL 10BIT 24SOIC"
"U6","AS6C8008_TSOPII","datasheets/AS6C8008.pdf","000_LOCAL:TSOP-II-44","1","","AS6C8008-55ZIN","IC SRAM 1Mx8 PARALLEL TSOP-II-44"
"U7","1G32","datasheets/LVC1G32.pdf","000_LOCAL:SOT-353_SC-70-5","1","","74LVC1G32GW,125","IC GATE OR 1CH 2-INP 5TSSOP"
